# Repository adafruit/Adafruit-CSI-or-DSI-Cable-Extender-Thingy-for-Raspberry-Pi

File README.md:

## Adafruit CSI or DSI Cable Extender Thingy for Raspberry Pi PCB

<a href="http://www.adafruit.com/products/3671"><br/>
Click here to purchase one from the Adafruit shop</a>

Thingy! Extender! Format is EagleCAD schematic and board layout

For more details, check out the product page at
* http://www.adafruit.com/product/3671

### Description

Every time someone posts on the Adafruit forums and says they need to have a really long cable for their Pi Camera (CSI) or Pi Display (DSI), we say, "Oh you mean like some sort of CSI/DSI cable extender thingy? Yeah we don't have one of those in stock yet" But that time is over! Now we can say, "Yes we have a CSI/DSI Cable Extender Thingy in stock!" And we point them here.

This Thingy is very simple, it lets you connect two 15-pin 1.0mm pitch cables end-to-end and extend the length. It does the funky pin rearranging and all for you, so just snap those two cables in. Carefully pry the two ears of the connectors, plug the cables with contacts pointing up, and then push the ears back in for a solid connection.

In theory, the CSI/DSI interface isn't meant for super long cables, and you're not supposed to extend them. But we laugh in the face of theory. We connected two 1 meter long extension cables using this Thingy and our Display and Camera worked! But, just so you know, it's really not guaranteed: CSI/DSI are meant for maybe 25cm max length.

For use with classic 15-pin 1.0mm pitch flex cables, does not fit the Pi Zero's skinny CSI connector.

### License

Adafruit invests time and resources providing this open source design, please support Adafruit and open-source hardware by purchasing products from [Adafruit](https://www.adafruit.com)!

Designed by Limor Fried/Ladyada for Adafruit Industries.

Creative Commons Attribution/Share-Alike, all text above must be included in any redistribution. See license.txt for additional details.

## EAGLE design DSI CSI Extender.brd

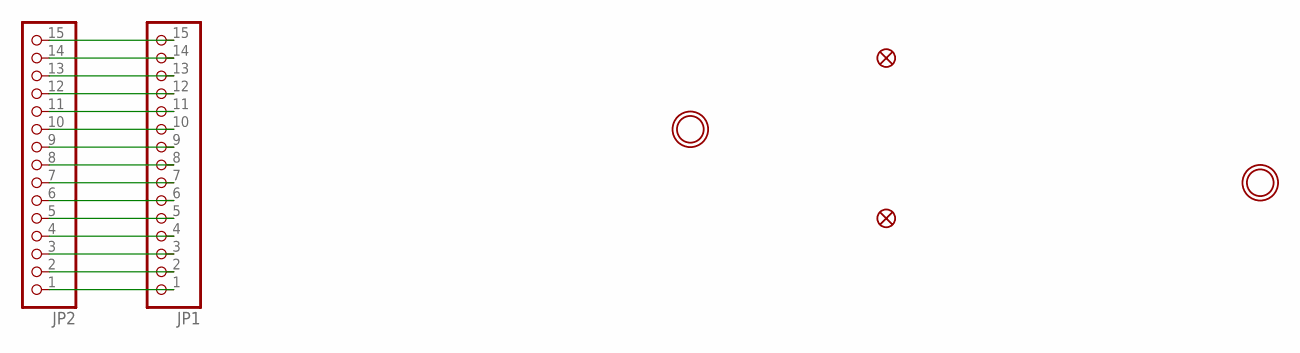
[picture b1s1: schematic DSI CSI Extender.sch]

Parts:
FID1, FID2: FIDUCIAL_1MM
JP1, JP2: HEADER-1X15_FPC1MM_PI; FPC_15PIN_1.0MM
U$2, U$3: MOUNTINGHOLE2.5; MOUNTINGHOLE_2.5_PLATED

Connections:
unnamed: JP1.1, JP2.1
unnamed: JP1.2, JP2.2
unnamed: JP1.3, JP2.3
unnamed: JP1.4, JP2.4
unnamed: JP1.5, JP2.5
unnamed: JP1.6, JP2.6
unnamed: JP1.7, JP2.7
unnamed: JP1.8, JP2.8
unnamed: JP1.9, JP2.9
unnamed: JP1.10, JP2.10
unnamed: JP1.11, JP2.11
unnamed: JP1.12, JP2.12
unnamed: JP1.13, JP2.13
unnamed: JP1.14, JP2.14
unnamed: JP1.15, JP2.15

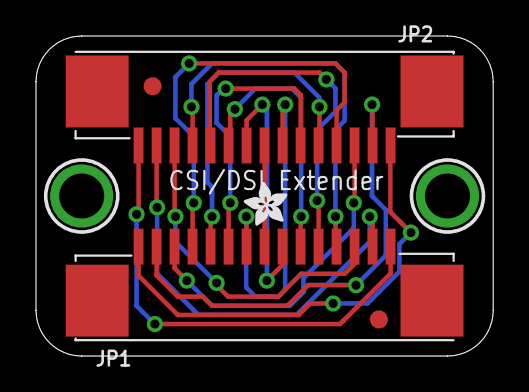
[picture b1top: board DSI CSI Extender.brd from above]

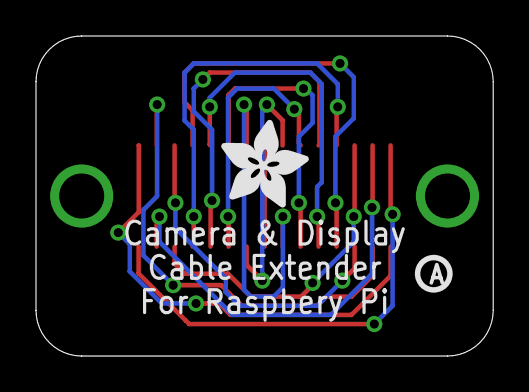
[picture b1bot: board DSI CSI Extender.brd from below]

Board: 2 copper layers, 25.4 x 17.8 mm, 9 parts (2 on the bottom side), 15 nets.

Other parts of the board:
U$4: ADAFRUIT_2.5MM
U$5: ADAFRUIT_5MM
U$6: PCBFEAT-REV-040

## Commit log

2017-11-21 thingy
2017-11-22 Correct Title

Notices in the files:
parts and their libraries:
microbuilder: This work is placed in the public domain, and may be freely used for commercial and non-commercial work with the following conditions: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
